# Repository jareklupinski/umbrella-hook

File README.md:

# umbrella-hook
Umbrella hook is a wall-mounted umbrella docking solution that interacts with AI-enhanced Weather Forecasting Services to notify the user of impending sky hydration by emitting a pleasing blue glow.

The intention is that as you glance at your umbrella on your way out the door, if the umbrella-hook is blue, you grab your umbrella.

## How it works

Umbrella-hook contains a small circuit board running a simple program that:
- Offers an interface for connecting umbrella-hook to a WiFi router and setting the umbrella-hook location
- Makes a GET request with the provided location to an API that responds with whether there will be rain in that area, and in how many hours

The umbrella-hook then turns on the on-board LED if the returned hours value overlaps the user's chosen "Rain Warning Time" (default to 6 hours).

Housing:

Housing Wireframe:

Circuit Board:

Schematic:

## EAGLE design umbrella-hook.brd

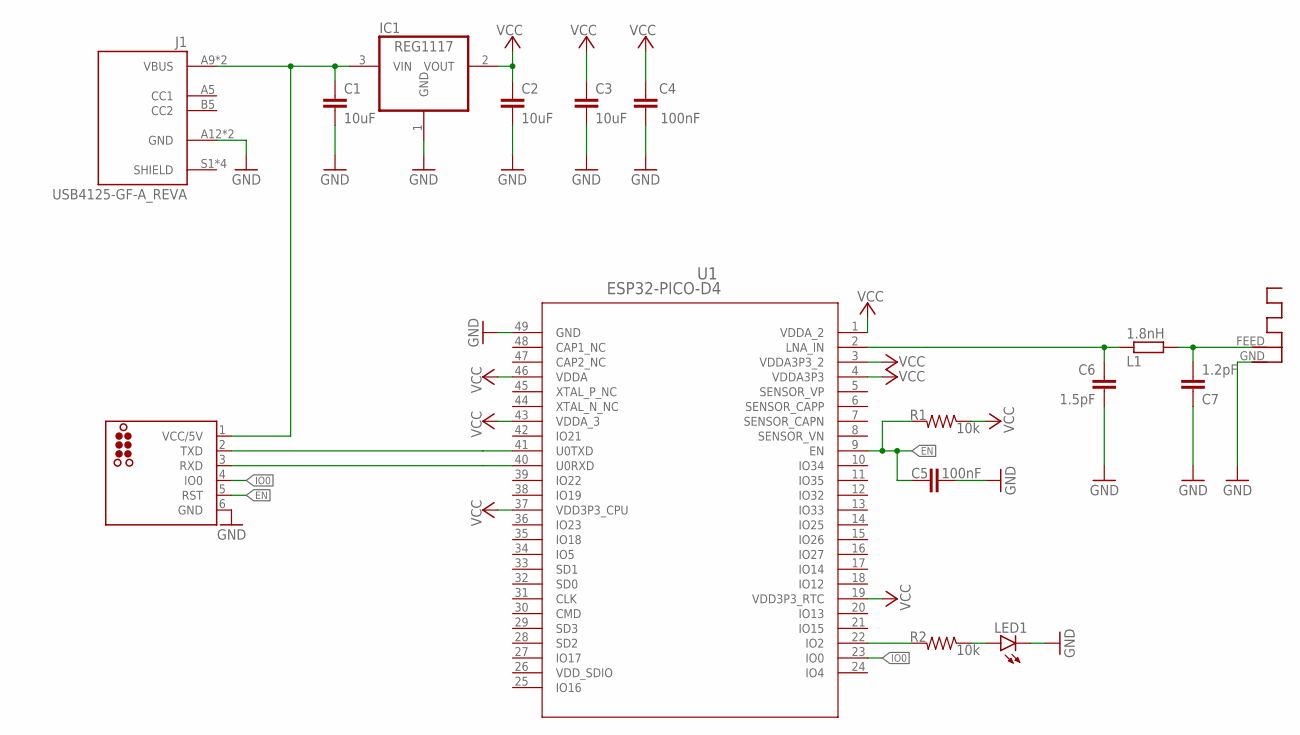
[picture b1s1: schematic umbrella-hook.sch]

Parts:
ANT1: ANTENNA; RN-ANT
C1, C2, C3: 10uF; C0805
C4, C5: 100nF; C0402
C6: 1.5pF; C0402
C7: 1.2pF; C0402
IC1: REG1117; SOT223
J1: USB4125-GF-A_REVA; GCT_USB4125-GF-A_REVA
J2: TC2030-ESP; TC2030-MCP
L1: 1.8nH; R0402
LED1: LEDCHIP-LED0603; CHIP-LED0603
R1, R2: 10k; R0402
U1: ESP32-PICO-D4; ESP32-PICO-D4_EXP

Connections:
EN: C5.2, J2.5 (RST), R1.2, U1.9 (EN)
GND: ANT1.GND, C1.2, C2.2, C3.2, C4.2, C5.1, C6.2, C7.1, IC1.1 (GND), J1.A12 (GND), J1.B12 (GND), J2.6 (GND), LED1.C, U1.49 (GND)
IO0: J2.4 (IO0), U1.23 (IO0)
unnamed: ANT1.FEED, C7.2, L1.2
unnamed: C6.1, L1.1, U1.2 (LNA_IN)
unnamed: R2.2, U1.22 (IO2)
unnamed: LED1.A, R2.1
unnamed: C1.1, IC1.3 (VIN), J1.A9 (VBUS), J1.B9 (VBUS), J2.1 (VCC/5V)
unnamed: J2.2 (TXD), U1.41 (U0TXD)
unnamed: J2.3 (RXD), U1.40 (U0RXD)
VCC: C2.1, C3.1, C4.1, IC1.2 (VOUT), R1.1, U1.1 (VDDA_2), U1.3 (VDDA3P3_2), U1.4 (VDDA3P3), U1.19 (VDD3P3_RTC), U1.37 (VDD3P3_CPU), U1.43 (VDDA_3), U1.46 (VDDA)
VDD_SDIO: U1.26 (VDD_SDIO)

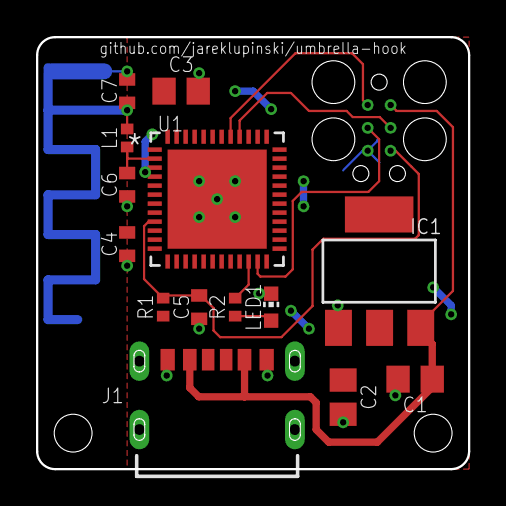
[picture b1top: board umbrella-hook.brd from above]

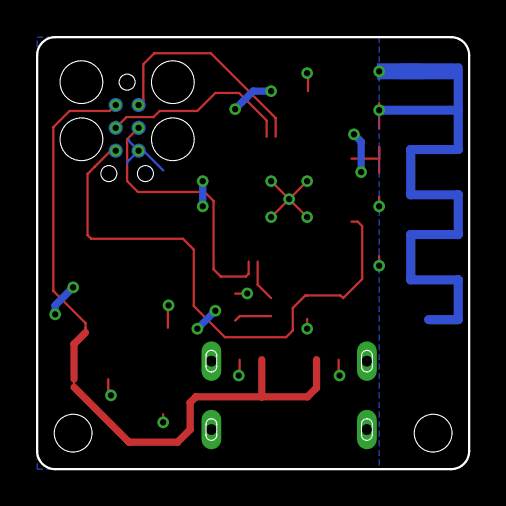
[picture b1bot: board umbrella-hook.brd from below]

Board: 2 copper layers, 24.0 x 24.0 mm, 16 parts (2 on the bottom side), 11 nets.

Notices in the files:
parts and their libraries:
tag-connect: ©2009 ROFA.cz - modified and updated by Robert Darlington ‹rdarlington@gmail.com›
COPYRIGHT: Copyright (C) 2018 Accelerated Designs. All rights reserved
